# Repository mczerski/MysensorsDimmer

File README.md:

# MysensorsDimmer

Led dimmer board that can be controlled with local switches and remotely witch NRF24L01 RF module. It is based on the Arduino Pro Mini board and is intended to be used with MySensors library.

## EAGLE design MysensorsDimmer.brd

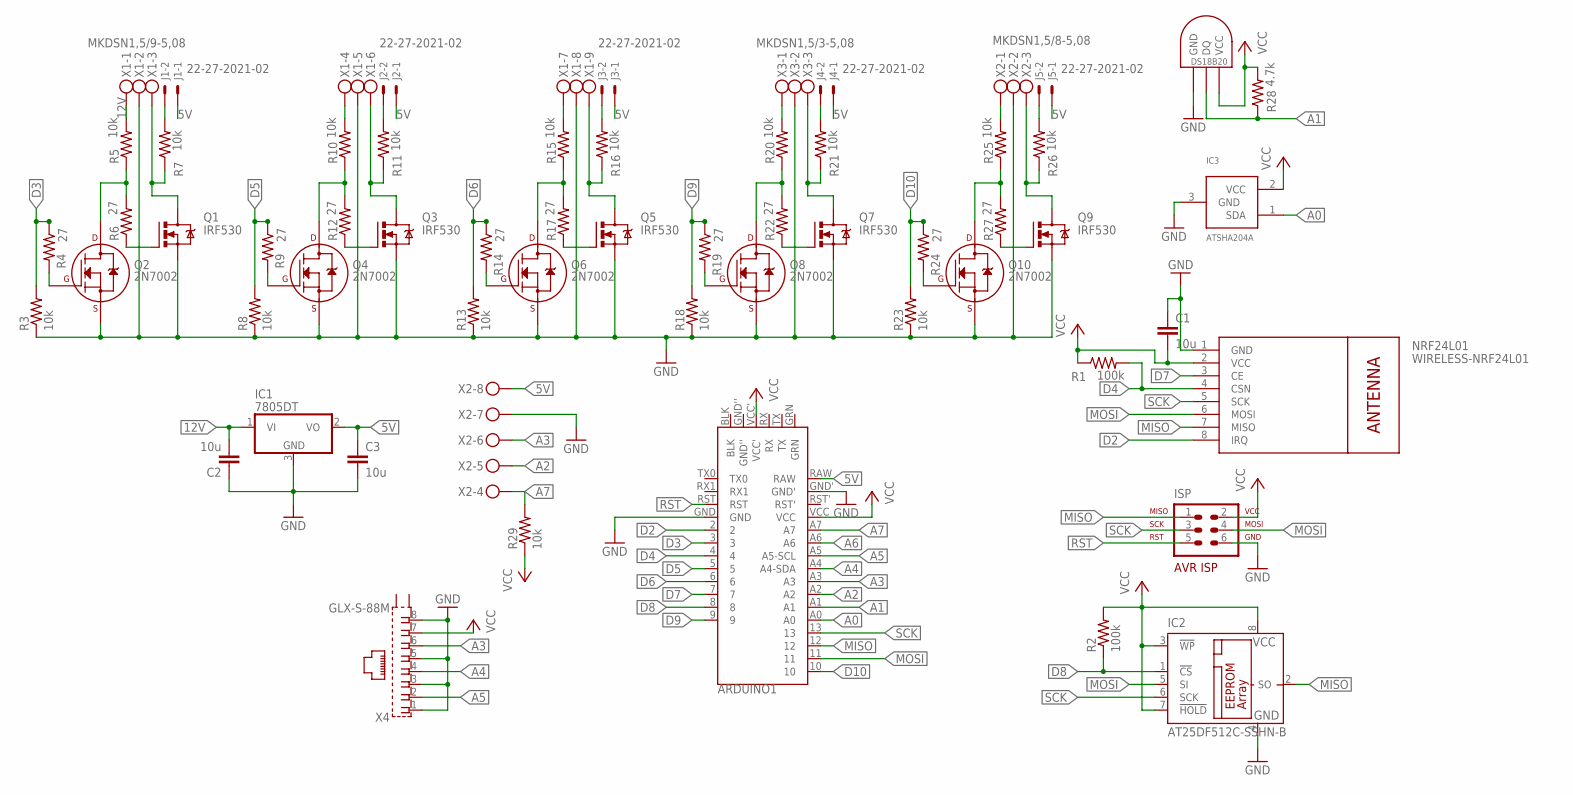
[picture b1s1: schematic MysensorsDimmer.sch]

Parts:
ARDUINO1: ARDUINO_PRO_MINI_V1
C1, C3: 10u; 0603-CAP
C2: 10u; 1206
IC1: 7805DT; TO252
IC2: AT25DF512C-SSHN-B; SO-08
IC3: ATSHA204A; SOT23
IC4: DS1820; µSOP8
ISP: N/M; AVR-ISP-6
J1, J2, J3, J4, J5: 22-27-2021-02; 6410-02
NRF24L01: WIRELESS-NRF24L01
Q1, Q3, Q5, Q7, Q9: IRF530; TO220BV
Q2, Q4, Q6, Q8, Q10: 2N7002; SOT-23
R1, R2: 100k; 0603-RES
R3, R5, R7, R8, R10, R11, R13, R15, R16, R18, R20, R21, R23, R25, R26, R29: 10k; 0603-RES
R4, R6, R9, R12, R14, R17, R19, R22, R24, R27: 27; 0603-RES
R28: 4.7k; 0603-RES
X1: MKDSN1,5/9-5,08
X2: MKDSN1,5/8-5,08
X3: MKDSN1,5/3-5,08
X4: GLX-S-88M

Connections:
5V: ARDUINO1.RAW, C3.1, IC1.2 (VO), J1.1, J2.1, J3.1, J4.1, J5.1, X2.8
12V: C2.2, IC1.1 (VI), R5.2, X1.1
A0: ARDUINO1.A0, IC3.1 (SDA)
A1: ARDUINO1.A1, IC4.1 (DQ), R28.1
A2: ARDUINO1.A2, X2.5
A3: ARDUINO1.A3, X2.6, X4.6
A4: ARDUINO1.A4 (A4-SDA), X4.4
A5: ARDUINO1.A5 (A5-SCL), X4.2
A6: ARDUINO1.A6
A7: ARDUINO1.A7, R29.2, X2.4
D2: ARDUINO1.2, NRF24L01.8 (IRQ)
D3: ARDUINO1.3, R3.2, R4.1
D4: ARDUINO1.4, NRF24L01.4 (CSN), R1.2
D5: ARDUINO1.5, R8.2, R9.1
D6: ARDUINO1.6, R13.2, R14.1
D7: ARDUINO1.7, NRF24L01.3 (CE)
D8: ARDUINO1.8, IC2.1 (!CS), R2.1
D9: ARDUINO1.9, R18.2, R19.1
D10: ARDUINO1.10, R23.2, R24.1
GND: ARDUINO1.GND, ARDUINO1.GND', C1.1, C2.1, C3.2, IC1.3 (GND), IC2.4 (GND), IC3.3 (GND), IC4.4 (GND), ISP.6, NRF24L01.1 (GND), Q1.S, Q2.2 (S), Q3.S, Q4.2 (S), Q5.S, Q6.2 (S), Q7.S, Q8.2 (S), Q9.S, Q10.2 (S), R3.1, R8.1, R13.1, R18.1, R23.1, X1.2, X1.5, X1.8, X2.2, X2.7, X3.2, X4.1, X4.3, X4.5, X4.8
MISO: ARDUINO1.12, IC2.2 (SO), ISP.1, NRF24L01.7 (MISO)
MOSI: ARDUINO1.11, IC2.5 (SI), ISP.4, NRF24L01.6 (MOSI)
unnamed: Q3.D, R11.1, X1.6
unnamed: Q1.G, R6.1
unnamed: Q4.1 (G), R9.2
unnamed: Q4.3 (D), R10.1, R12.2
unnamed: Q2.1 (G), R4.2
unnamed: Q3.G, R12.1
unnamed: J2.2, R11.2
unnamed: Q2.3 (D), R5.1, R6.2
unnamed: J1.2, R7.2
unnamed: Q5.D, R16.1, X1.9
unnamed: Q6.1 (G), R14.2
unnamed: Q6.3 (D), R15.1, R17.2
unnamed: Q5.G, R17.1
unnamed: J3.2, R16.2
unnamed: Q7.D, R21.1, X3.3
unnamed: Q8.1 (G), R19.2
unnamed: Q8.3 (D), R20.1, R22.2
unnamed: Q7.G, R22.1
unnamed: J4.2, R21.2
unnamed: Q9.D, R26.1, X2.3
unnamed: Q10.1 (G), R24.2
unnamed: Q1.D, R7.1, X1.3
unnamed: Q10.3 (D), R25.1, R27.2
unnamed: Q9.G, R27.1
unnamed: J5.2, R26.2
unnamed: R10.2, X1.4
unnamed: R15.2, X1.7
unnamed: R20.2, X3.1
unnamed: R25.2, X2.1
RST: ARDUINO1.RST, ISP.5
SCK: ARDUINO1.13, IC2.6 (SCK), ISP.3, NRF24L01.5 (SCK)
VCC: ARDUINO1.VCC, ARDUINO1.VCC', C1.2, IC2.3 (!WP), IC2.7 (!HOLD), IC2.8 (VCC), IC3.2 (VCC), IC4.8 (VCC), ISP.2, NRF24L01.2 (VCC), R1.1, R2.2, R28.2, R29.1, X4.7

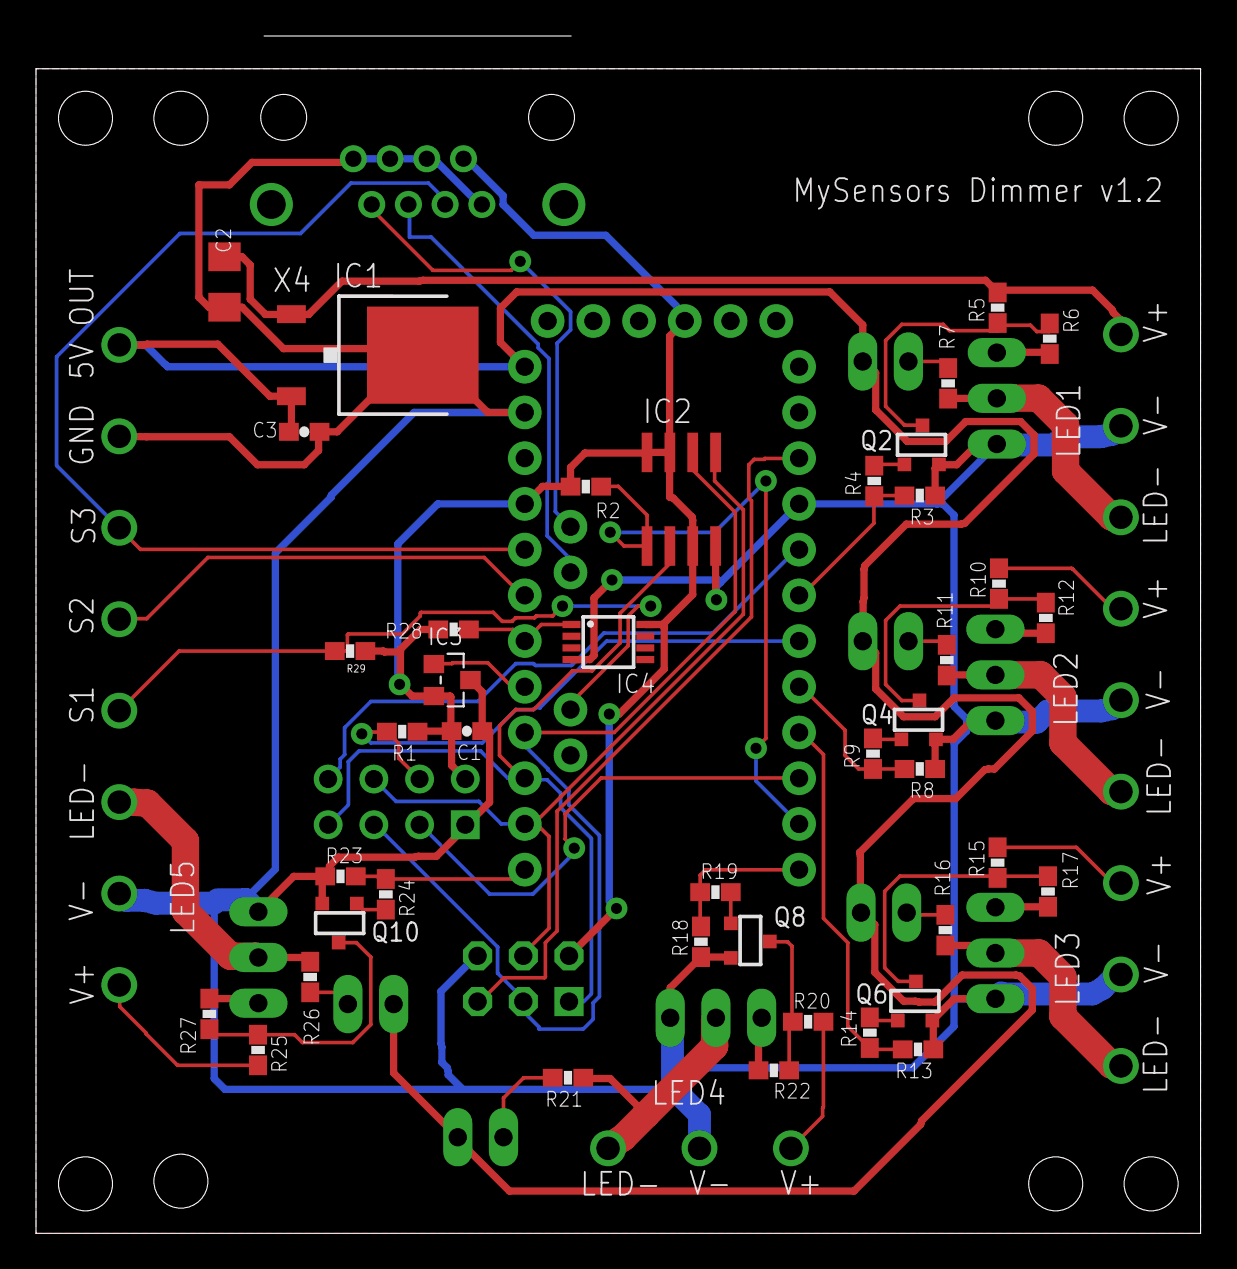
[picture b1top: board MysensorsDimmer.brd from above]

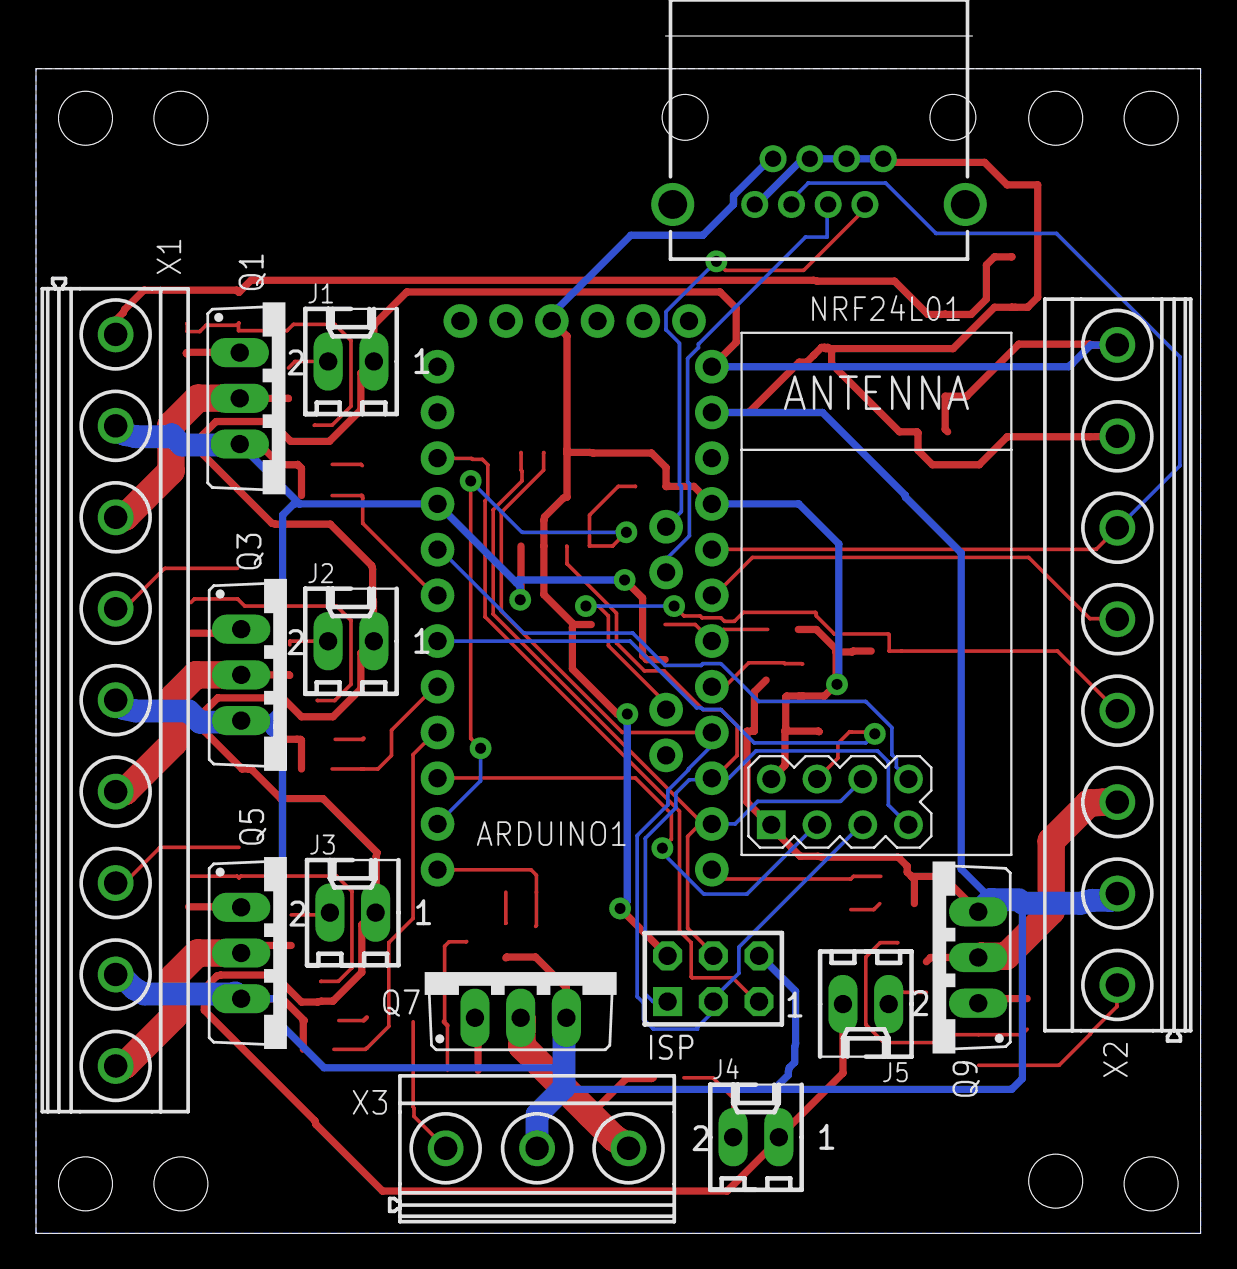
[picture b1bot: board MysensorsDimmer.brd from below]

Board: 2 copper layers, 64.7 x 66.5 mm, 58 parts (16 on the bottom side), 53 nets.

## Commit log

2017-06-05 initial version
2017-06-05 corrected descriptions and holes positions
2017-06-05 modifications after v1.0 version (see changelog.txt)
2017-06-05 adapted to SUPERTRONIC PP83N enclosure + corrected nrf module position in relation to screw connectors (they were overlaping)
2017-06-05 corrected descriptions, names, etc.
2017-07-18 fix mounting hole position
2017-07-21 add i2c connection for apds 9930
2017-07-23 version update

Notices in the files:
parts and their libraries:
SparkFun-Passives: Licensing: Creative Commons ShareAlike 4.0 International - https://creativecommons.org/licenses/by-sa/4.0
diy-modules: Released under the Creative Commons Attribution 4.0 International License: http://creativecommons.org/licenses/by/4.0
